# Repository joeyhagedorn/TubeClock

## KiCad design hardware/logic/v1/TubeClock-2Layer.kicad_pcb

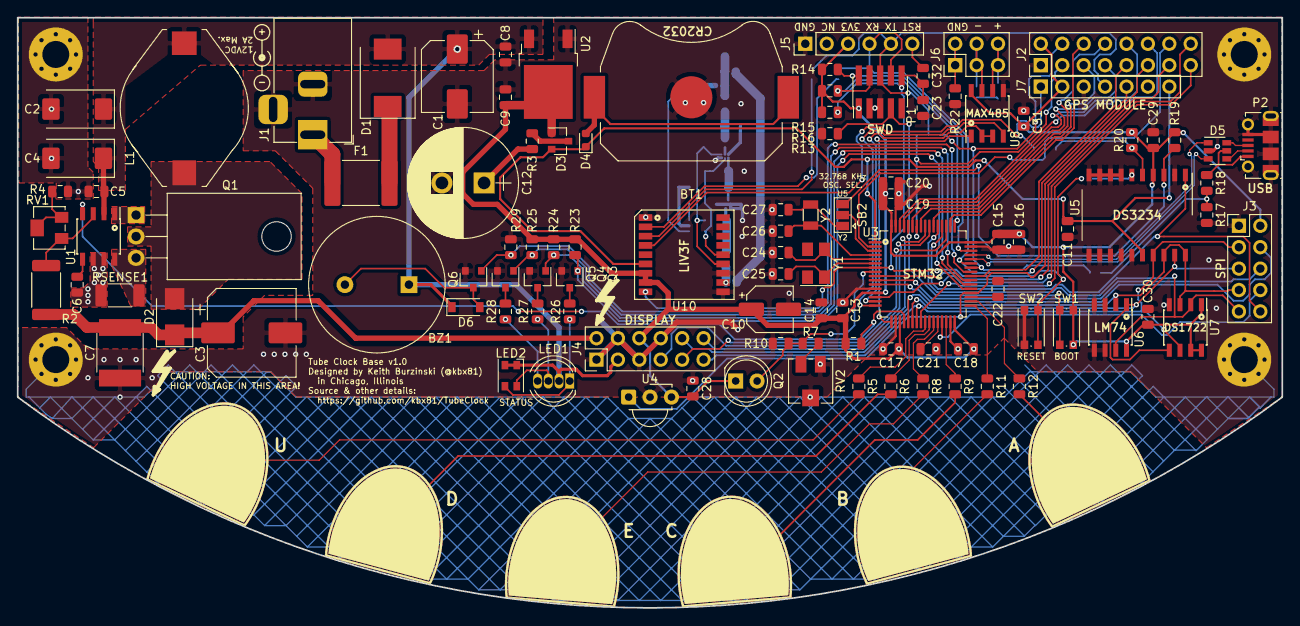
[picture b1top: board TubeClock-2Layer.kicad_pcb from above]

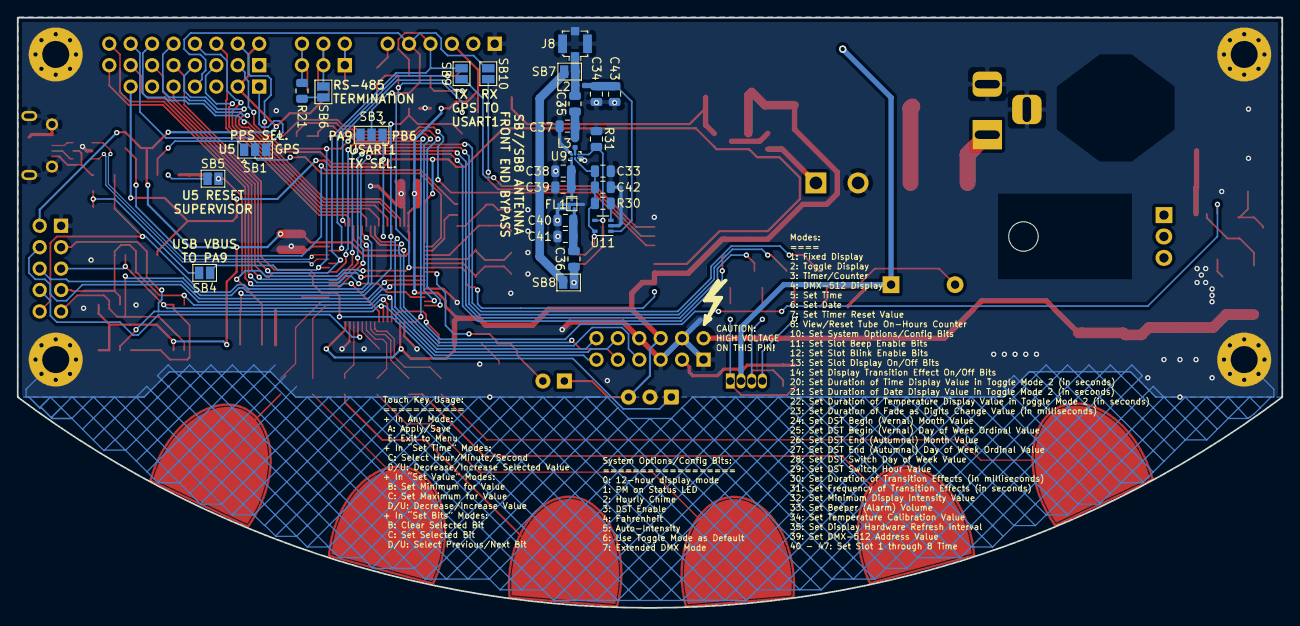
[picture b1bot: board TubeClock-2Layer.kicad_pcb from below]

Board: 2 copper layers, 150.0 x 70.0 mm, 143 parts (29 on the bottom side), 111 nets.

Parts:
BT1: CR2032; BatteryHolder_Keystone_3034_1x20mm
BZ1: Buzzer; Buzzer_16x14RM7.6
C1: 100 uF; CP_Elec_8x10
C2: 100 uF 35 V; CP_EIA-7343-31_Kemet-D
C3: 4.7 uF; CP_Elec_10x10
C4: 10 uF 25 V; CP_EIA-7343-31_Kemet-D
C5, C6, C8, C11, C15, C17, C18, C19, C23, C28, C29, C30, C31, C32: 100 nF; C_0805_2012Metric
C7: 100 nF 250 V; C_2420_HandSoldering
C9, C42: 10 uF; C_0805_2012Metric
C10: 100 uF; CP_Elec_5x5.3
C12: 470 mF; CP_Radial_D13.0mm_P5.00mm_HD1.5mm
C13: 10 nF; C_0805_2012Metric
C14: 1 uF; C_0805_2012Metric
C16, C20: 4.7 uF; C_0805_2012Metric
C21, C22: 47 nF; C_0805_2012Metric
C24, C25: 10 pF; C_0805_2012Metric
C26, C27: 12.5 pF; C_0805_2012Metric
C33, C43: 1 nF; C_0805_2012Metric
C34, C35, C36: 120 pF; C_0805_2012Metric
C37, C38, C39, C40, C41: 3.9 pF; C_0805_2012Metric
D1: S3A; D_SMC
D2: ES2F; D_SMB
D3: BAT64-04; SOT-23
D4: BAT64-02V; D_0603_1608Metric
D5: USBLC6; SOT-23-6
D6: 1N4148; D_SOD-123
F1: ~{2A}; Fuse_2920_7451Metric
FL1: B39162B4327P810; Filter_1411-5_1.4x1.1mm
H1, H2, H3, H4: MountingHole_Pad; MountingHole_3.2mm_M3_Pad_Via
J1: Jack-DC; BarrelJack_Horizontal
J2: Conn_02x08_Odd_Even; PinHeader_2x08_P2.54mm_Vertical
J3: Conn_02x05_Odd_Even; PinHeader_2x05_P2.54mm_Vertical
J4: Conn_02x06_Odd_Even; PinHeader_2x06_P2.54mm_Vertical
J5: Conn_01x06; PinHeader_1x06_P2.54mm_Vertical
J6: Conn_02x03_Odd_Even; PinHeader_2x03_P2.54mm_Vertical
J7: Conn_01x07; PinHeader_1x07_P2.54mm_Vertical
J8: Conn_Coaxial; U.FL_Molex_MCRF_73412-0110_Vertical
L1: 100µH 2A; L_EPCOS_B82479A1_Handsoldering
L2: 100 nH; L_0402_1005Metric
L3: L; L_0402_1005Metric
LED1: LED_RGB_COMMON_ANODE; LED_D5.0mm-4_RGB
LED2: LED_Dual_AACC; LED_Cree-PLCC4_3.2x2.8mm_CCW
P1: STM32_SWD_USART; PinHeader_2x05_P1.27mm_Vertical_SMD
P2: CONN_MICRO_USB_B; USB_Micro-B_Molex-105017-0001
Q1: IRF644PBF; TO-220-3_Horizontal_TabDown
Q2: Q_Photo_NPN; LED_D5.0mm_Clear
Q3, Q4, Q5, Q6: 2N7002; SOT-23
R1, R30: 100K; R_0805_2012Metric
R2: 1.5M; R_2512_6332Metric
R3: 56Ω 0.5W; R_0805_2012Metric
R4, R7, R13, R14, R15, R16, R19, R20, R31: 10K; R_0805_2012Metric
R5, R6, R8, R9, R11, R12, R26, R27, R28: 1K; R_0805_2012Metric
R10, R23, R24, R25, R29: 1M; R_0805_2012Metric
R17: 68K; R_0805_2012Metric
R18: 47K; R_0805_2012Metric
R21: 120; R_0805_2012Metric
R22: 0; R_0805_2012Metric
RSENSE1: .05; R_2010_5025Metric
RV1: 5K; Potentiometer_Bourns_3214W_Vertical
RV2: 100K; Potentiometer_Vishay_TS53YJ_Vertical
SB1, SB2, SB3: GS3; SolderJumper-3_P1.3mm_Open_Pad1.0x1.5mm
SB4, SB5, SB6, SB7, SB8, SB9, SB10: GS2; SolderJumper-2_P1.3mm_Open_Pad1.0x1.5mm
SW1, SW2: SW_Push; SW_Push_1P1T_NO_CK_KMR2
TP1: TouchPad; TouchPad1
TP2: TouchPad2; TouchPad1
TP3: TouchPad3; TouchPad1
TP4: TouchPad4; TouchPad1
TP5: TouchPad5; TouchPad1
TP6: TouchPad6; TouchPad1
U1: MAX1771; SOIC-8_3.9x4.9mm_P1.27mm
U2: LD1117S33TR; TO-252-2
U3: STM32F072RBTx; LQFP-64_10x10mm_P0.5mm
U4: TSOP382xx; Vishay_MINICAST-3Pin
U5: DS3234; SO-20_12.8x7.5mm_P1.27mm
U6: LM74; SOIC-8_3.9x4.9mm_P1.27mm
U7: DS1722; SOIC-8_3.9x4.9mm_P1.27mm
U8: MAX485E; SOIC-8_3.9x4.9mm_P1.27mm
U9: BGA824N6; TSNP-6-2_1.2x0.8mm
U10: Teseo-LIV3F; LCC-18
U11: TPS22943; SOT-353_SC-70-5
Y1: 8 MHz; Crystal_SMD_5032-4Pin_5.0x3.2mm
Y2: 32.768 KHz; Crystal_SMD_3215-2Pin_3.2x1.5mm

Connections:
+3V3: C9.1, C10.1, C13.1, C14.1, C15.1, C16.1, C17.1, C18.1, C19.1, C20.1, C28.1, C29.1, C30.2, C31.1, D3.1, J2.2, J3.2, J4.6, J5.3, J7.2, P1.1, Q2.1, R1.1, R14.1, R15.1, R16.1, R19.2, R20.2, R23.1, R24.1, R25.1, SW1.2, U2.2, U3.13, U3.19, U3.32, U3.48, U3.64, U4.3, U5.4, U6.8, U7.1, U7.7, U7.8, U8.8, U10.7, U10.8
+BATT: C11.1, D3.2, D4.1, J7.7, U3.1, U5.16, U10.6
+V_ANT: C34.1, C43.2, L2.1, U11.1
+V_HV: C3.1, C7.1, D2.1, J4.2, R2.1
+V_IN: BZ1.1, C1.1, C2.1, C4.1, C5.1, C8.1, D1.2, D6.1, J4.3, L1.1, LED1.2, LED2.1, LED2.2, U1.2, U2.3
+V_RF: C33.1, C42.2, R30.1, U9.2, U10.14, U11.5
/TubeClock-Display/BLANK: J4.7, U3.55
/TubeClock-Display/SPI1_MISO_DISP: J4.12, U3.56
/TubeClock-Display/SPI1_MOSI: J3.3, J4.11, U3.23, U5.17, U7.6
/TubeClock-Display/SPI1_NSS_DISP: J4.9, U3.51
/TubeClock-Display/SPI1_SCK: J3.7, J4.10, U3.21, U5.18, U5.20, U6.2, U7.3
/TubeClock-GPS/RESET: C23.1, C32.2, P1.10, R16.2, SB5.1, SW2.2, U3.7, U10.9
/TubeClock-GPS/SQW_OUT_GPS: J7.1, SB1.3, U10.4
/TubeClock-GPS/USART1_RX: J5.4, J7.5, P1.8, SB9.2, U3.43
/TubeClock-GPS/USART1_TX: J5.5, J7.4, P1.6, SB3.2, SB10.2
/TubeClock-MCU/BEEP: Q6.1, R29.1, U3.41
/TubeClock-MCU/LED0: Q3.1, R23.2, U3.37
/TubeClock-MCU/LED1: Q4.1, R24.2, U3.38
/TubeClock-MCU/LED2: Q5.1, R25.2, U3.39
/TubeClock-MCU/OSC32_IN: R19.1, SB2.3, U5.3
/TubeClock-MCU/SHUTDOWN: R1.2, U1.4, U3.20
/TubeClock-MCU/SPI1_MISO: J3.5, U3.22, U5.19, U6.1, U7.5
/TubeClock-MCU/SPI1_NSS_RTC: J3.10, U3.52, U5.1
/TubeClock-MCU/SPI1_NSS_TEMP: J3.9, U3.53, U6.7, U7.2
/TubeClock-MCU/SPI2_MISO: J3.6, U3.10
/TubeClock-MCU/SPI2_MOSI: J3.4, U3.11
/TubeClock-MCU/SPI2_SCK: J3.8, U3.29
/TubeClock-MCU/SQW_IN: J2.14, SB1.2, U3.2
/TubeClock-MCU/USART2_MODE: U3.15, U8.2, U8.3
/TubeClock-MCU/USART2_RX: U3.17, U8.1
/TubeClock-MCU/USART2_TX: U3.16, U8.4
/TubeClock-Peripherals/SQW_OUT_RTC: R20.1, SB1.1, U5.5
ADC_IN: Q2.2, R7.1, R10.1, U3.8
ANT_OFF: R31.1, U9.6, U10.13, U11.4
BOOT0: P1.7, R13.2, SW1.1, U3.60
G3_CS: C21.1, U3.28
G3_K1: R5.1, U3.25
G3_K2: R6.1, U3.26
G3_K3: R8.1, U3.27
G6_CS: C22.1, U3.35
G6_K1: R9.1, U3.30
G6_K2: R11.1, U3.33
G6_K3: R12.1, U3.34
GND: BT1.2, C1.2, C2.2, C3.2, C4.2, C5.2, C6.2, C7.2, C8.2, C9.2, C10.2, C11.2, C12.2, C13.2, C14.2, C15.2, C16.2, C17.2, C18.2, C19.2, C20.2, C21.2, C22.2, C23.2, C24.2, C25.2, C26.1, C27.2, C28.2, C29.2, C30.1, C31.2, C33.2, C34.2, C37.1, C38.2, C39.2, C40.2, C41.2, C42.1, C43.1, D5.2, FL1.2, FL1.3, FL1.5, H1.1, H2.1, H3.1, H4.1, J1.2, J1.3, J2.1, J3.1, J4.1, J4.4, J4.5, J4.8, J5.1, J7.3, J8.2, P1.3, P1.5, P2.5, P2.6, Q3.2, Q4.2, Q5.2, Q6.2, R4.2, R10.2, R13.1, R17.1, R22.2, R29.2, R31.2, RSENSE1.2, RV2.2, RV2.3, SW2.1, U1.6, U1.7, U2.1, U3.12, U3.18, U3.31, U3.47, U3.63, U4.2, U5.2, U5.7, U5.8, U5.9, U5.10, U5.11, U5.12, U5.13, U5.14, U5.15, U6.3, U6.4, U6.5, U6.6, U7.4, U8.5, U9.1, U9.4, U10.1, U10.10, U10.12, U11.2
unnamed: BT1.1, D4.2
unnamed: BZ1.2, D6.2, Q6.3
unnamed: C6.1, U1.5
unnamed: C12.1, R3.1
unnamed: C24.1, U3.5, Y1.2
unnamed: C25.1, U3.6, Y1.1
unnamed: C26.2, U3.4, Y2.1
unnamed: C27.1, SB2.1, Y2.2
unnamed: C32.1, J5.6
unnamed: C35.1, C37.2, L3.1
unnamed: C35.2, J8.1, L2.2, SB7.2
unnamed: C36.1, SB8.2, U10.11
unnamed: C36.2, C40.1, C41.1, FL1.4
unnamed: C38.1, C39.1, FL1.1, U9.3
unnamed: D1.1, F1.1
unnamed: D2.2, L1.2, Q1.2
unnamed: D3.3, R3.2
unnamed: D5.4, P2.2
unnamed: D5.5, P2.1, R18.1
unnamed: D5.6, P2.3
unnamed: F1.2, J1.1
unnamed: J6.1, J6.2, R22.1
unnamed: J6.3, J6.4, SB6.1, U8.7
unnamed: J6.5, J6.6, R21.1, U8.6
unnamed: L3.2, U9.5
unnamed: LED1.1, LED2.3, R26.1
unnamed: LED1.3, LED2.4, R27.2
unnamed: LED1.4, R28.2
unnamed: Q1.1, U1.1
unnamed: Q1.3, RSENSE1.1, U1.8
unnamed: Q3.3, R26.2
unnamed: Q4.3, R27.1
unnamed: Q5.3, R28.1
unnamed: R2.2, RV1.1, U1.3
unnamed: R4.1, RV1.2, RV1.3
unnamed: R5.2, TP1.1
unnamed: R6.2, TP2.1
unnamed: R7.2, RV2.1
unnamed: R8.2, TP3.1
unnamed: R9.2, TP4.1
unnamed: R11.2, TP5.1
unnamed: R12.2, TP6.1
unnamed: R17.2, R18.2, SB4.2
unnamed: R21.2, SB6.2
unnamed: R30.2, U11.3
unnamed: SB2.2, U3.3
unnamed: SB5.2, U5.6
unnamed: SB7.1, SB8.1
unnamed: SB9.1, U10.2
unnamed: SB10.1, U10.3
STM32_PA0: J2.16, U3.14
STM32_PA9: J2.4, SB3.3, SB4.1, U3.42
STM32_PA15: J2.6, U3.50
STM32_PB5: J2.8, U3.57
STM32_PB6: J2.3, SB3.1, U3.58
STM32_PB7: J2.7, U3.59
STM32_PB8: J2.10, U3.61
STM32_PB9: J2.12, U3.62
STM32_PB15: J2.11, U3.36, U4.1
STM32_PC1: J2.13, U3.9
STM32_PC4: J2.15, U3.24
STM32_PC9: J2.9, U3.40
STM32_PD2: J2.5, U3.54
SYS_SWCLK: P1.4, R15.2, U3.49
SYS_SWDIO: P1.2, R14.2, U3.46
USB+: D5.1, U3.45
USB-: D5.3, U3.44

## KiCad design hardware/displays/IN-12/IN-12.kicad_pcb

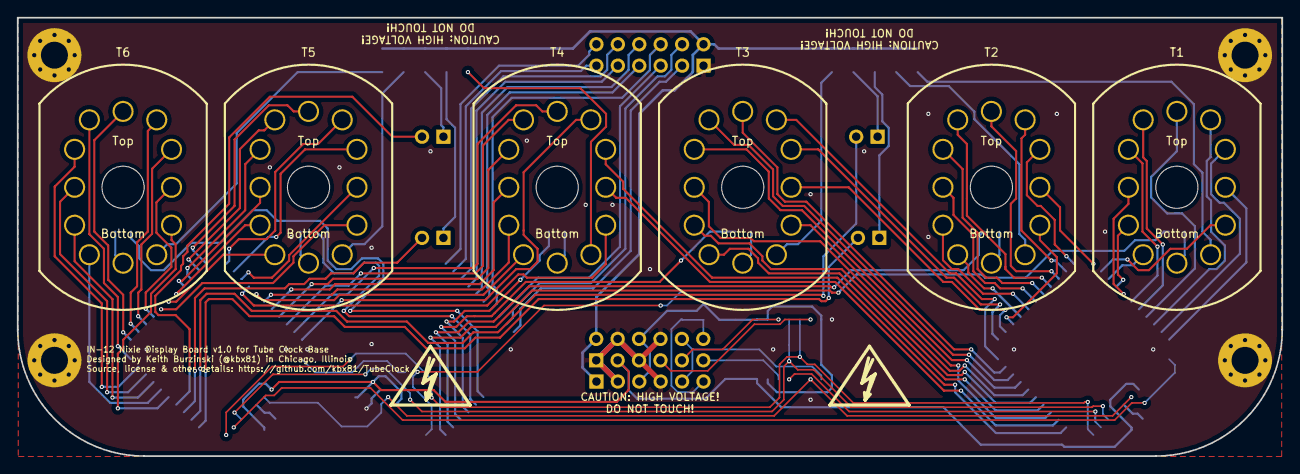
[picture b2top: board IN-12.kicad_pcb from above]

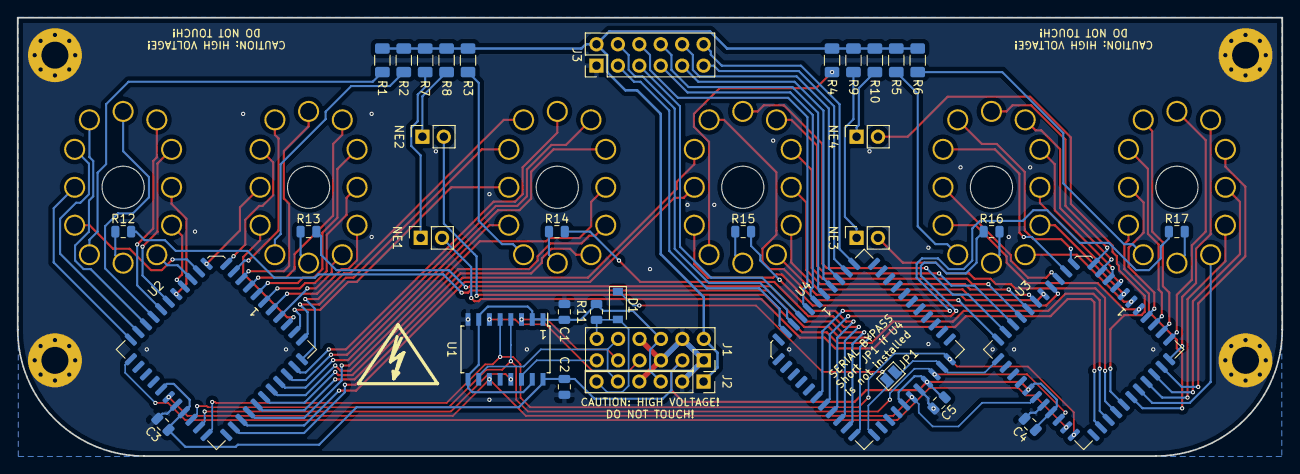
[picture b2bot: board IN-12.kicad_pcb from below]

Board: 2 copper layers, 150.0 x 52.0 mm, 45 parts (35 on the bottom side), 112 nets.

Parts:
C1, C2, C3, C4, C5: 100 nF; C_0805_2012Metric
D1: 1N4148; D_SOD-123
H1, H2, H3, H4: MountingHole_Pad; MountingHole_3.2mm_M3_Pad_Via
J1: Conn_02x06_Odd_Even; PinSocket_2x06_P2.54mm_Vertical
J2: Conn_01x06; PinSocket_1x06_P2.54mm_Vertical
J3: Conn_02x06_Odd_Even; PinHeader_2x06_P2.54mm_Vertical
JP1: SolderJumper_2_Open; SolderJumper-2_P1.3mm_Open_Pad1.0x1.5mm
NE1, NE2, NE3, NE4: Lamp_Neon; PinSocket_1x02_P2.54mm_Vertical
R1, R2, R3, R4, R5, R6: 10K; R_1206_3216Metric
R7, R8, R9, R10: 470K; R_1206_3216Metric
R11, R12, R13, R14, R15, R16, R17: 10K; R_0805_2012Metric
T1, T2, T3, T4, T5, T6: IN-12B_Nixie_Tube; Nixie_IN-12
U1: CD40109B; SOIC-16W_5.3x10.2mm_P1.27mm
U2, U3, U4: HV5622; PLCC-44_16.6x16.6mm_P1.27mm

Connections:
+3V3: C1.1, J1.6, J2.3, R11.1, U1.1, U1.2, U1.7, U1.9, U1.15
+V_HV: J1.2, J2.1, J3.2, R1.2, R2.2, R3.2, R4.2, R5.2, R6.2, R7.2, R8.2, R9.2, R10.2
+V_IN: C2.1, C3.1, C4.1, C5.1, J1.3, U1.16, U2.22, U2.25, U3.22, U3.25, U4.22, U4.25
CLK: U1.11, U2.23, U3.23, U4.23
CLK_DB: J1.10, J2.5, U1.10
DATA_IN: U1.13, U2.27
DATA_IN_DB: J1.11, U1.14
DATA_OUT: D1.1, JP1.2, U4.18
DATA_OUT_DB: D1.2, J1.12, J2.6, R11.2
DATA_THROUGH1: U2.18, U3.27
DATA_THROUGH2: JP1.1, U3.18, U4.27
EXT1: J3.3, U4.5
EXT2: J3.4, U4.4
EXT3: J3.5, U4.3
EXT4: J3.6, U4.2
EXT5: J3.7, U4.1
EXT6: J3.8, U4.44
EXT7: J3.9, U4.43
EXT8: J3.10, U4.42
EXT9: J3.11, U4.41
EXT10: J3.12, U4.40
GND: C1.2, C2.2, C3.2, C4.2, C5.2, H1.1, H2.1, H3.1, H4.1, J1.1, J1.4, J1.5, J1.8, J2.2, J2.4, J3.1, U1.8, U2.24, U3.24, U4.24
unnamed: NE1.1, R7.1
unnamed: NE2.1, R8.1
unnamed: NE3.1, R9.1
unnamed: NE4.1, R10.1
unnamed: R1.1, T1.1
unnamed: R2.1, T2.1
unnamed: R3.1, T3.1
unnamed: R4.1, T4.1
unnamed: R5.1, T5.1
unnamed: R6.1, T6.1
unnamed: R12.1, U4.17
unnamed: R13.1, U4.16
unnamed: R14.1, U4.15
unnamed: R15.1, U4.14
unnamed: R16.1, U4.13
unnamed: R17.1, U4.12
T1_K_0: T1.2, U2.8
T1_K_1: T1.11, U2.9
T1_K_2: T1.10, U2.10
T1_K_3: T1.9, U2.11
T1_K_4: T1.8, U2.12
T1_K_5: T1.7, U2.13
T1_K_6: T1.6, U2.14
T1_K_7: T1.5, U2.15
T1_K_8: T1.4, U2.16
T1_K_9: T1.3, U2.17
T1_PL: R12.2, T1.12
T2_K_0: T2.2, U2.42
T2_K_1: T2.11, U2.43
T2_K_2: T2.10, U2.44
T2_K_3: T2.9, U2.1
T2_K_4: T2.8, U2.2
T2_K_5: T2.7, U2.3
T2_K_6: T2.6, U2.4
T2_K_7: T2.5, U2.5
T2_K_8: T2.4, U2.6
T2_K_9: T2.3, U2.7
T2_PL: R13.2, T2.12
T3_K_0: T3.2, U2.32
T3_K_1: T3.11, U2.33
T3_K_2: T3.10, U2.34
T3_K_3: T3.9, U2.35
T3_K_4: T3.8, U2.36
T3_K_5: T3.7, U2.37
T3_K_6: T3.6, U2.38
T3_K_7: T3.5, U2.39
T3_K_8: T3.4, U2.40
T3_K_9: T3.3, U2.41
T3_PL: R14.2, T3.12
T4_K_0: T4.2, U3.10
T4_K_1: T4.11, U3.11
T4_K_2: T4.10, U3.12
T4_K_3: T4.9, U3.13
T4_K_4: T4.8, U3.14
T4_K_5: T4.7, U3.15
T4_K_6: T4.6, U3.16
T4_K_7: T4.5, U3.17
T4_K_8: T4.4, U2.30
T4_K_9: T4.3, U2.31
T4_PL: R15.2, T4.12
T5_K_0: T5.2, U3.44
T5_K_1: T5.11, U3.1
T5_K_2: T5.10, U3.2
T5_K_3: T5.9, U3.3
T5_K_4: T5.8, U3.4
T5_K_5: T5.7, U3.5
T5_K_6: T5.6, U3.6
T5_K_7: T5.5, U3.7
T5_K_8: T5.4, U3.8
T5_K_9: T5.3, U3.9
T5_PL: R16.2, T5.12
T6_K_0: T6.2, U3.34
T6_K_1: T6.11, U3.35
T6_K_2: T6.10, U3.36
T6_K_3: T6.9, U3.37
T6_K_4: T6.8, U3.38
T6_K_5: T6.7, U3.39
T6_K_6: T6.6, U3.40
T6_K_7: T6.5, U3.41
T6_K_8: T6.4, U3.42
T6_K_9: T6.3, U3.43
T6_PL: R17.2, T6.12
T7_K: NE1.2, U3.30
T8_K: NE2.2, U3.31
T9_K: NE3.2, U3.32
T10_K: NE4.2, U3.33
~BL_DB: J1.7, U1.6
~BL: U1.5, U2.28, U3.28, U4.28
~LE_DB: J1.9, U1.3
~LE: U1.4, U2.26, U3.26, U4.26

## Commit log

2024-10-11 Add B5991 display board
2024-10-11 Latest changes in ToT, might not want all of these
2024-10-15 Fix errant 1 on silkscreen
2024-12-19 All latest produced changes
